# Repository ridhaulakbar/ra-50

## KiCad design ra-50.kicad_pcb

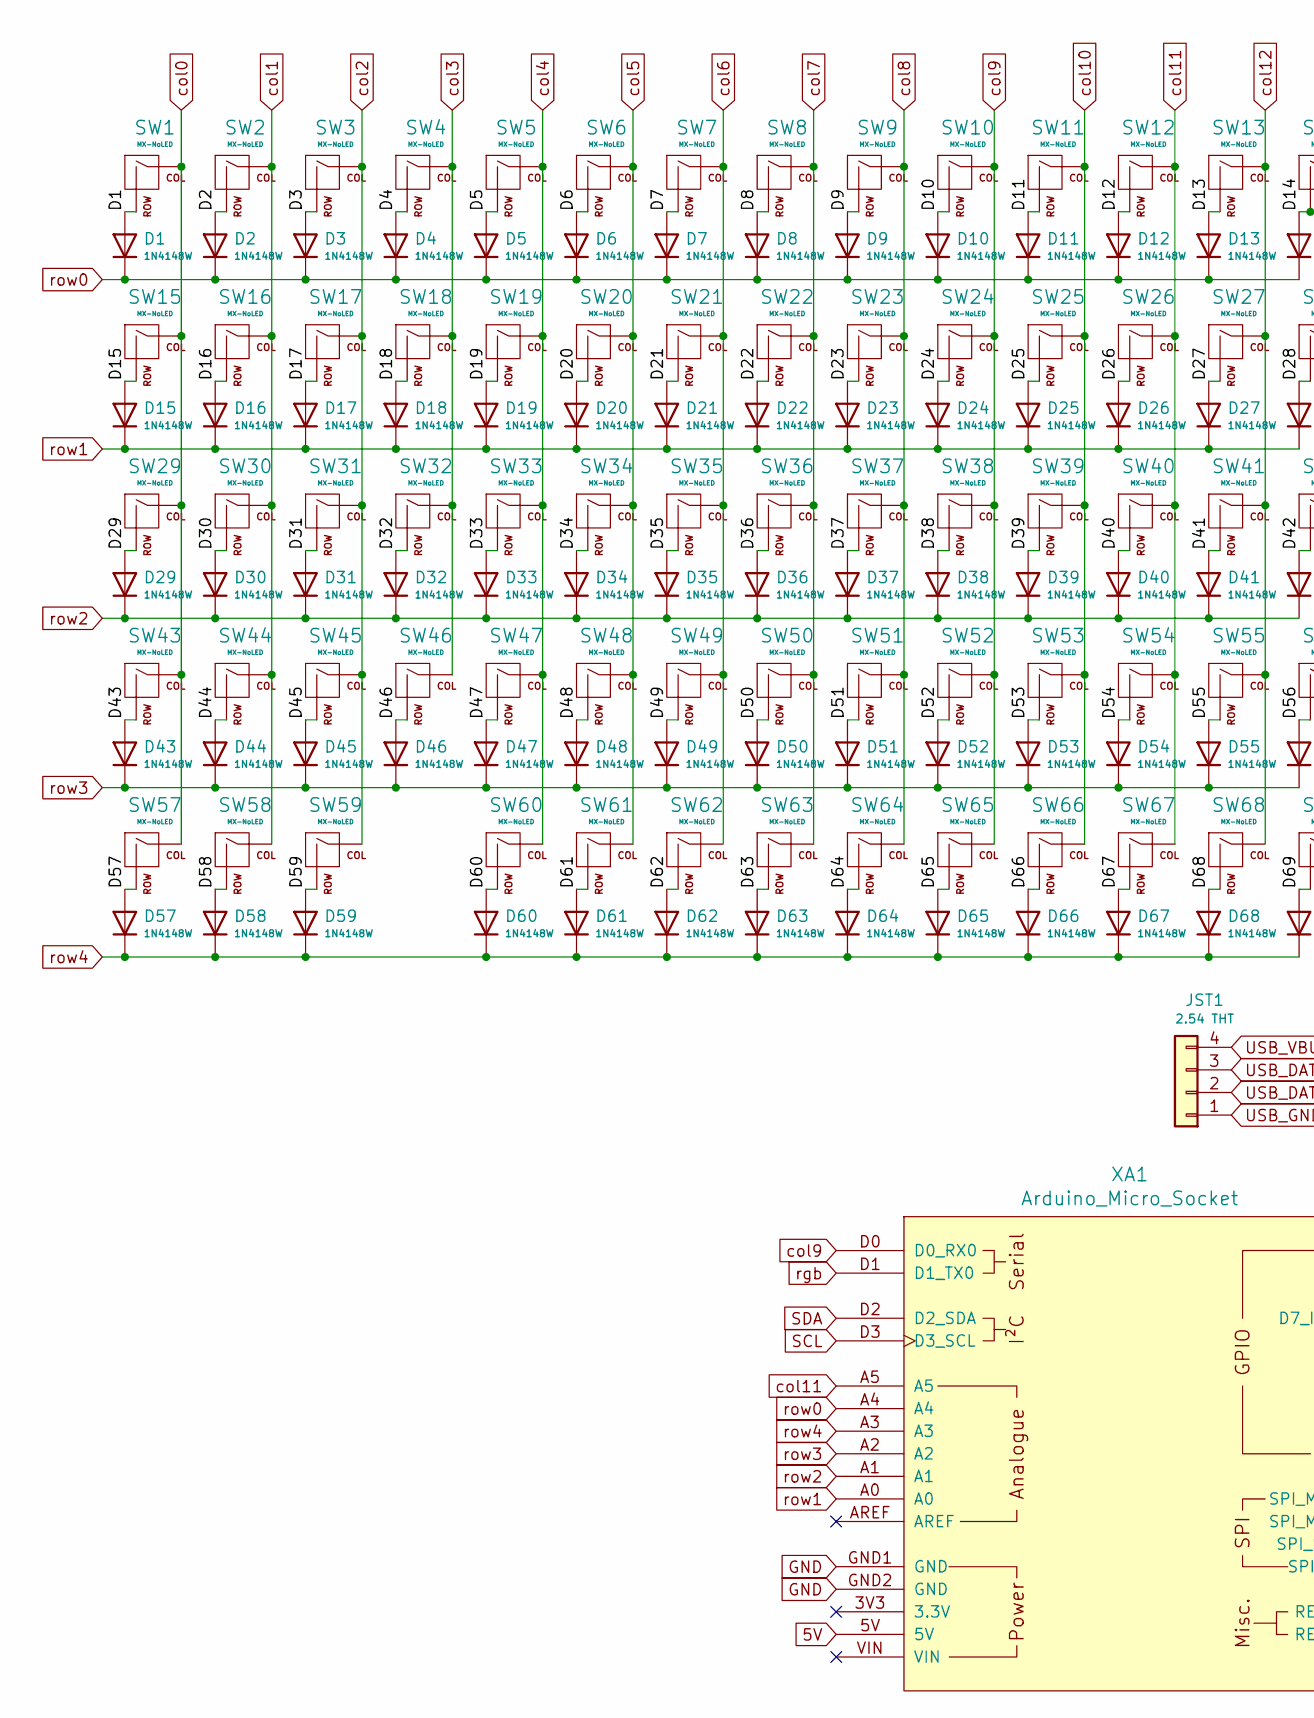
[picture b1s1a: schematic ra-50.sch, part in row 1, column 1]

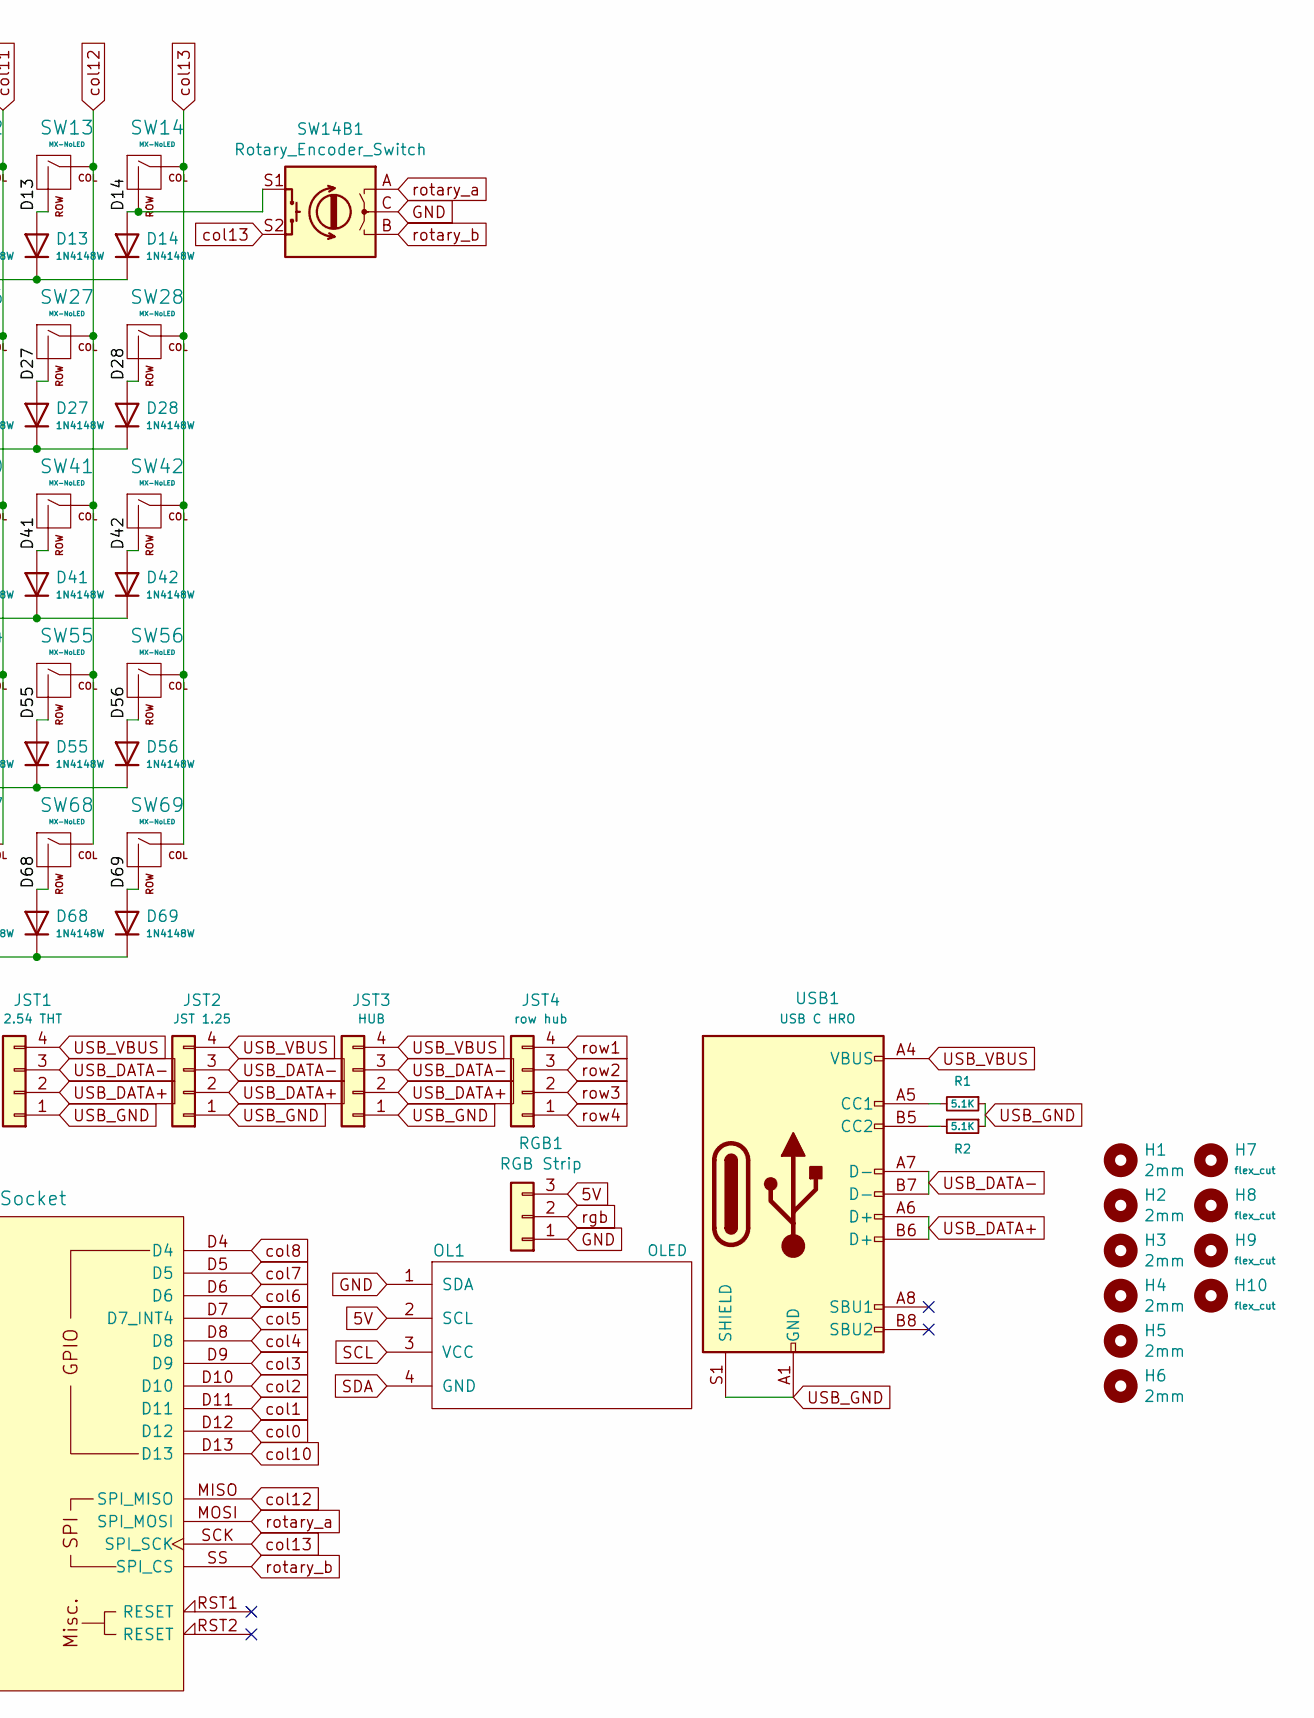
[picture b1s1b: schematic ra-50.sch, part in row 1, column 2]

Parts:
D1, D2, D3, D4, D5, D6, D7, D8, D9, D10, D11, D12, D13, D14, D15, D16, D17, D18, D19, D20, D21, D22, D23, D24, D25, D26, D27, D28, D29, D30, D31, D32, D33, D34, D35, D36, D37, D38, D39, D40, D41, D42, D43, D44, D45, D46, D47, D48, D49, D50, D51, D52, D53, D54, D55, D56, D57, D58, D59, D60, D61, D62, D63, D64, D65, D66, D67, D68, D69: 1N4148W; D_SOD123
H1, H2, H3, H4, H5, H6: 2mm; 2mm_hole
H7, H8, H9, H10: flex_cut; LongOvalCut_225mmFlexCut
JST1: 2.54 THT; PinHeader_1x04_P2.54mm_Vertical
JST2: JST 1.25; JST_GH_SM04B-GHS-TB_1x04-1MP_P1.25mm_Horizontal
JST3: HUB; PinHeader_1x04_P2.54mm_Vertical
JST4: row hub; PinHeader_1x04_P1.00mm_Vertical
OL1: OLED; SSD1306-0.91-OLED-4pin-128x32
R1, R2: 5.1K; R_0603_1608Metric_Pad0.98x0.95mm_HandSolder
RGB1: RGB Strip; PinSocket_1x03_P2.54mm_Vertical
SW1, SW2, SW3, SW4, SW5, SW6, SW7, SW8, SW9, SW10, SW11, SW12, SW13, SW14, SW15, SW16, SW17, SW18, SW19, SW20, SW21, SW22, SW23, SW24, SW25, SW26, SW27, SW28, SW29, SW30, SW31, SW32, SW33, SW34, SW35, SW36, SW37, SW38, SW39, SW40, SW41, SW42, SW43, SW44, SW45, SW46, SW47, SW48, SW49, SW50, SW51, SW52, SW53, SW54, SW55, SW56, SW57, SW58, SW59, SW60, SW61, SW62, SW63, SW64, SW65, SW66, SW67, SW68, SW69: MX-NoLED; CherryMX_ChocV2_1u
SW14B1: Rotary_Encoder_Switch; RotaryEncoder_Alps_EC11E-Switch_Vertical_H20mm
USB1: USB C HRO; USB_C_Receptacle_HRO_TYPE-C-31-M-12
XA1: Arduino_Micro_Socket

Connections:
5V: OL1.2 (SCL), RGB1.3, XA1.5V
/D1: D1.2 (A), SW1.2 (ROW)
/D2: D2.2 (A), SW2.2 (ROW)
/D3: D3.2 (A), SW3.2 (ROW)
/D4: D4.2 (A), SW4.2 (ROW)
/D5: D5.2 (A), SW5.2 (ROW)
/D6: D6.2 (A), SW6.2 (ROW)
/D7: D7.2 (A), SW7.2 (ROW)
/D8: D8.2 (A), SW8.2 (ROW)
/D9: D9.2 (A), SW9.2 (ROW)
/D10: D10.2 (A), SW10.2 (ROW)
/D11: D11.2 (A), SW11.2 (ROW)
/D12: D12.2 (A), SW12.2 (ROW)
/D13: D13.2 (A), SW13.2 (ROW)
/D14: D14.2 (A), SW14.2 (ROW), SW14B1.S1
/D15: D15.2 (A), SW15.2 (ROW)
/D16: D16.2 (A), SW16.2 (ROW)
/D17: D17.2 (A), SW17.2 (ROW)
/D18: D18.2 (A), SW18.2 (ROW)
/D19: D19.2 (A), SW19.2 (ROW)
/D20: D20.2 (A), SW20.2 (ROW)
/D21: D21.2 (A), SW21.2 (ROW)
/D22: D22.2 (A), SW22.2 (ROW)
/D23: D23.2 (A), SW23.2 (ROW)
/D24: D24.2 (A), SW24.2 (ROW)
/D25: D25.2 (A), SW25.2 (ROW)
/D26: D26.2 (A), SW26.2 (ROW)
/D27: D27.2 (A), SW27.2 (ROW)
/D28: D28.2 (A), SW28.2 (ROW)
/D29: D29.2 (A), SW29.2 (ROW)
/D30: D30.2 (A), SW30.2 (ROW)
/D31: D31.2 (A), SW31.2 (ROW)
/D32: D32.2 (A), SW32.2 (ROW)
/D33: D33.2 (A), SW33.2 (ROW)
/D34: D34.2 (A), SW34.2 (ROW)
/D35: D35.2 (A), SW35.2 (ROW)
/D36: D36.2 (A), SW36.2 (ROW)
/D37: D37.2 (A), SW37.2 (ROW)
/D38: D38.2 (A), SW38.2 (ROW)
/D39: D39.2 (A), SW39.2 (ROW)
/D40: D40.2 (A), SW40.2 (ROW)
/D41: D41.2 (A), SW41.2 (ROW)
/D42: D42.2 (A), SW42.2 (ROW)
/D43: D43.2 (A), SW43.2 (ROW)
/D44: D44.2 (A), SW44.2 (ROW)
/D45: D45.2 (A), SW45.2 (ROW)
/D46: D46.2 (A), SW46.2 (ROW)
/D47: D47.2 (A), SW47.2 (ROW)
/D48: D48.2 (A), SW48.2 (ROW)
/D49: D49.2 (A), SW49.2 (ROW)
/D50: D50.2 (A), SW50.2 (ROW)
/D51: D51.2 (A), SW51.2 (ROW)
/D52: D52.2 (A), SW52.2 (ROW)
/D53: D53.2 (A), SW53.2 (ROW)
/D54: D54.2 (A), SW54.2 (ROW)
/D55: D55.2 (A), SW55.2 (ROW)
/D56: D56.2 (A), SW56.2 (ROW)
/D57: D57.2 (A), SW57.2 (ROW)
/D58: D58.2 (A), SW58.2 (ROW)
/D59: D59.2 (A), SW59.2 (ROW)
/D60: D60.2 (A), SW60.2 (ROW)
/D61: D61.2 (A), SW61.2 (ROW)
/D62: D62.2 (A), SW62.2 (ROW)
/D63: D63.2 (A), SW63.2 (ROW)
/D64: D64.2 (A), SW64.2 (ROW)
/D65: D65.2 (A), SW65.2 (ROW)
/D66: D66.2 (A), SW66.2 (ROW)
/D67: D67.2 (A), SW67.2 (ROW)
/D68: D68.2 (A), SW68.2 (ROW)
/D69: D69.2 (A), SW69.2 (ROW)
GND: OL1.1 (SDA), RGB1.1, SW14B1.C, XA1.GND1 (GND), XA1.GND2 (GND)
unnamed: R1.2, USB1.A5 (CC1)
unnamed: R2.2, USB1.B5 (CC2)
SCL: OL1.3 (VCC), XA1.D3 (D3_SCL)
SDA: OL1.4 (GND), XA1.D2 (D2_SDA)
USB_DATA+: JST1.2, JST2.2, JST3.2, USB1.A6 (D+), USB1.B6 (D+)
USB_DATA-: JST1.3, JST2.3, JST3.3, USB1.A7 (D-), USB1.B7 (D-)
USB_GND: JST1.1, JST2.1, JST3.1, R1.1, R2.1, USB1.A1 (GND), USB1.A12 (GND), USB1.B1 (GND), USB1.B12 (GND), USB1.S1 (SHIELD)
USB_VBUS: JST1.4, JST2.4, JST3.4, USB1.A4 (VBUS), USB1.A9 (VBUS), USB1.B4 (VBUS), USB1.B9 (VBUS)
col0: SW1.1 (COL), SW15.1 (COL), SW29.1 (COL), SW43.1 (COL), SW57.1 (COL), XA1.D12
col1: SW2.1 (COL), SW16.1 (COL), SW30.1 (COL), SW44.1 (COL), SW58.1 (COL), XA1.D11
col2: SW3.1 (COL), SW17.1 (COL), SW31.1 (COL), SW45.1 (COL), SW59.1 (COL), XA1.D10
col3: SW4.1 (COL), SW18.1 (COL), SW32.1 (COL), SW46.1 (COL), XA1.D9
col4: SW5.1 (COL), SW19.1 (COL), SW33.1 (COL), SW47.1 (COL), SW60.1 (COL), XA1.D8
col5: SW6.1 (COL), SW20.1 (COL), SW34.1 (COL), SW48.1 (COL), SW61.1 (COL), XA1.D7 (D7_INT4)
col6: SW7.1 (COL), SW21.1 (COL), SW35.1 (COL), SW49.1 (COL), SW62.1 (COL), XA1.D6
col7: SW8.1 (COL), SW22.1 (COL), SW36.1 (COL), SW50.1 (COL), SW63.1 (COL), XA1.D5
col8: SW9.1 (COL), SW23.1 (COL), SW37.1 (COL), SW51.1 (COL), SW64.1 (COL), XA1.D4
col9: SW10.1 (COL), SW24.1 (COL), SW38.1 (COL), SW52.1 (COL), SW65.1 (COL), XA1.D0 (D0_RX0)
col10: SW11.1 (COL), SW25.1 (COL), SW39.1 (COL), SW53.1 (COL), SW66.1 (COL), XA1.D13
col11: SW12.1 (COL), SW26.1 (COL), SW40.1 (COL), SW54.1 (COL), SW67.1 (COL), XA1.A5
col12: SW13.1 (COL), SW27.1 (COL), SW41.1 (COL), SW55.1 (COL), SW68.1 (COL), XA1.MISO (SPI_MISO)
col13: SW14.1 (COL), SW14B1.S2, SW28.1 (COL), SW42.1 (COL), SW56.1 (COL), SW69.1 (COL), XA1.SCK (SPI_SCK)
rgb: RGB1.2, XA1.D1 (D1_TX0)
rotary_a: SW14B1.A, XA1.MOSI (SPI_MOSI)
rotary_b: SW14B1.B, XA1.SS (SPI_CS)
row0: D1.1 (K), D2.1 (K), D3.1 (K), D4.1 (K), D5.1 (K), D6.1 (K), D7.1 (K), D8.1 (K), D9.1 (K), D10.1 (K), D11.1 (K), D12.1 (K), D13.1 (K), D14.1 (K), XA1.A4
row1: D15.1 (K), D16.1 (K), D17.1 (K), D18.1 (K), D19.1 (K), D20.1 (K), D21.1 (K), D22.1 (K), D23.1 (K), D24.1 (K), D25.1 (K), D26.1 (K), D27.1 (K), D28.1 (K), JST4.4, XA1.A0
row2: D29.1 (K), D30.1 (K), D31.1 (K), D32.1 (K), D33.1 (K), D34.1 (K), D35.1 (K), D36.1 (K), D37.1 (K), D38.1 (K), D39.1 (K), D40.1 (K), D41.1 (K), D42.1 (K), JST4.3, XA1.A1
row3: D43.1 (K), D44.1 (K), D45.1 (K), D46.1 (K), D47.1 (K), D48.1 (K), D49.1 (K), D50.1 (K), D51.1 (K), D52.1 (K), D53.1 (K), D54.1 (K), D55.1 (K), D56.1 (K), JST4.2, XA1.A2
row4: D57.1 (K), D58.1 (K), D59.1 (K), D60.1 (K), D61.1 (K), D62.1 (K), D63.1 (K), D64.1 (K), D65.1 (K), D66.1 (K), D67.1 (K), D68.1 (K), D69.1 (K), JST4.1, XA1.A3

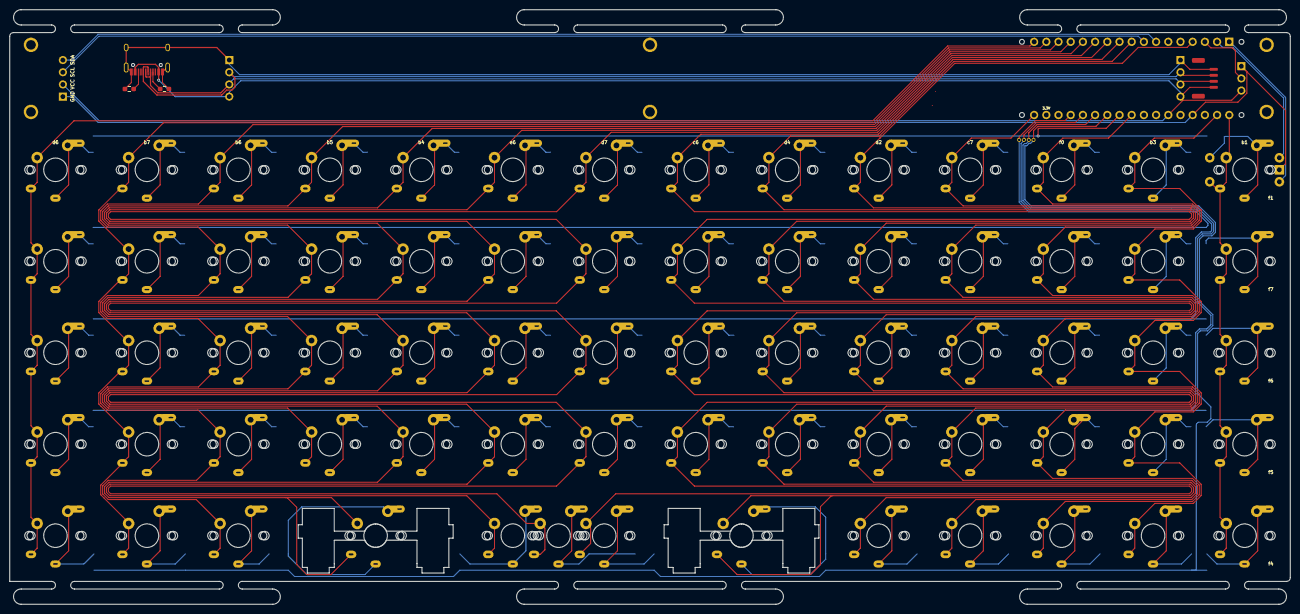
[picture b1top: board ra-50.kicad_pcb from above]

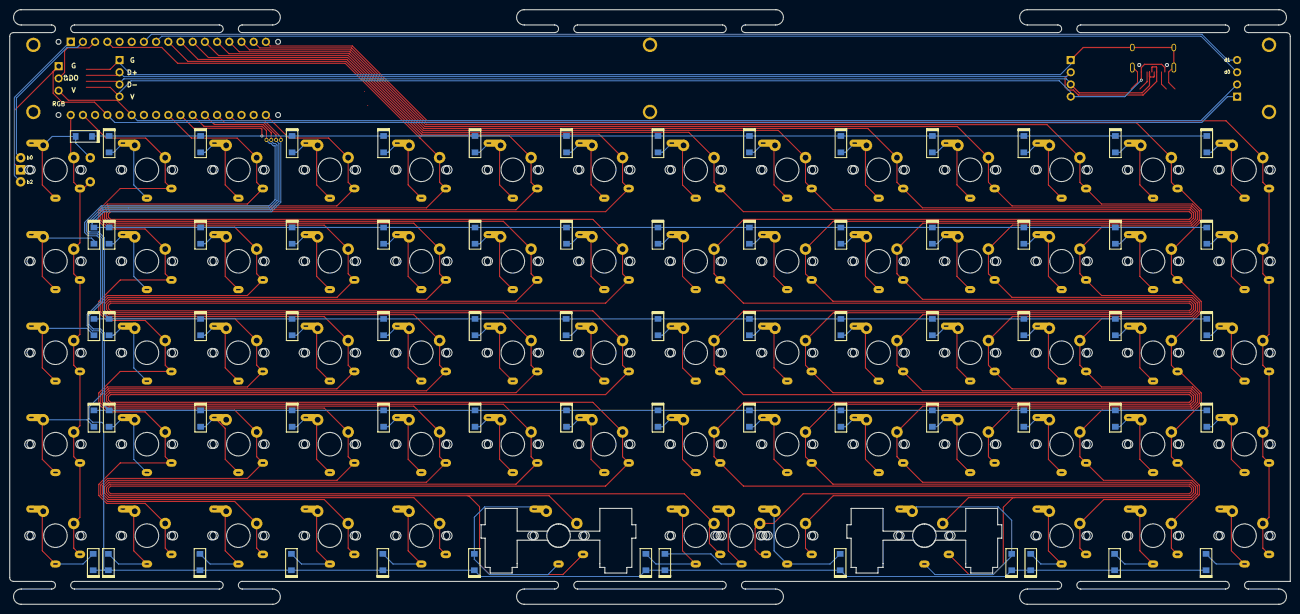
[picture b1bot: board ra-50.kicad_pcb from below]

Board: 2 copper layers, 266.7 x 123.8 mm, 159 parts (70 on the bottom side), 101 nets.

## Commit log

2021-07-15 few routing done
2021-07-16 add more track route
2021-07-17 add things, retrace, etc
2021-07-23 big revision
2021-07-24 final. or is it?
